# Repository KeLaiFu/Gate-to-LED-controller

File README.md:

# Gate-to-LED-controller
Edit of Jonathan Bedrava's LED controller (https://github.com/JonathanBedrava/eurorack-cv-led-strip-controller)

Current Status: Untested, although previous versions of an almost identical layout worked fine.

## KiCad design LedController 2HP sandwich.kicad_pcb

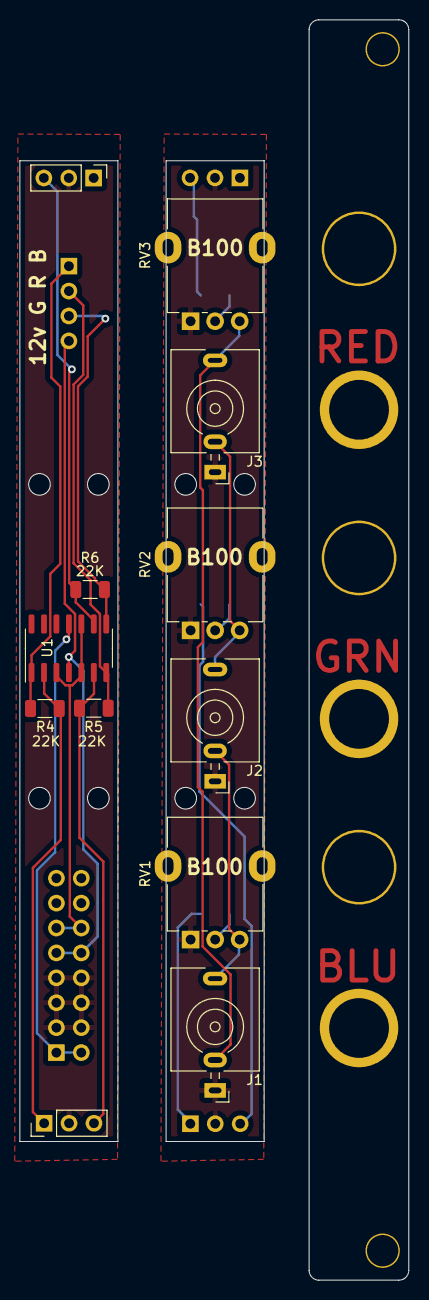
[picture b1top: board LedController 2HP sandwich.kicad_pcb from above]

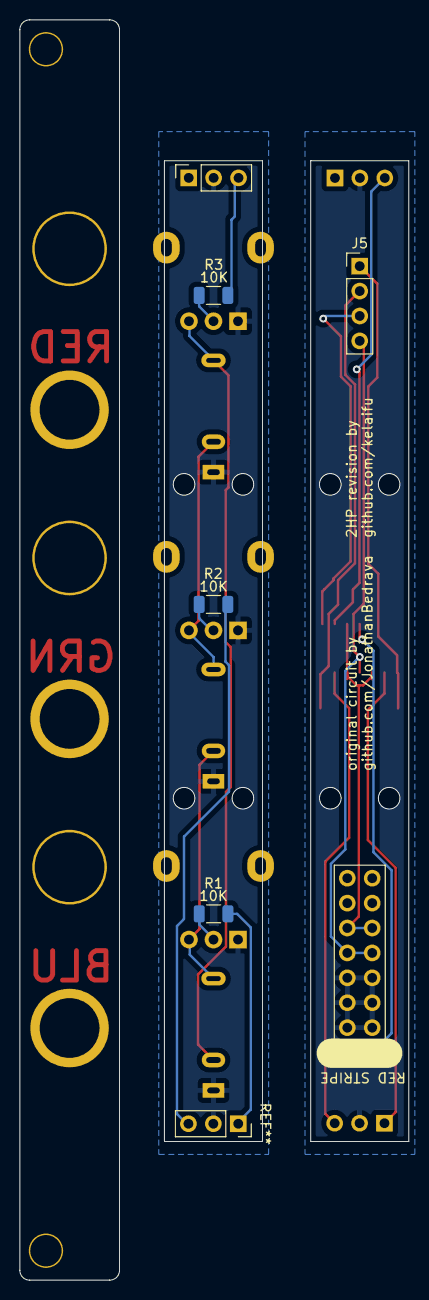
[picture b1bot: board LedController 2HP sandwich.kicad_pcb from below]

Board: 2 copper layers, 39.7 x 128.5 mm, 16 parts (5 on the bottom side), 16 nets.

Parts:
J1, J2, J3: AudioJack2; 3.5mm_tip_switch_thonkiconn
J4: Conn_02x08_Odd_Even; PinHeader_2x08_P2.54mm_Vertical
J5: Conn_01x04_Female; PinHeader_1x04_P2.54mm_Vertical
R1, R2, R3: 10K; R_1206_3216Metric
R4, R5, R6: 22K; R_1206_3216Metric
RV1, RV2, RV3: 100K; Potentiometer_Alpha_RD901F-40-00D_Single_Vertical
U1: TL084; SOIC-14_3.9x8.7mm_P1.27mm
U$1: EURORACK_PANEL2HP; EURORACK2HPPANEL

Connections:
+5V: J4.11, J4.12, U1.3 (+), U1.5 (+), U1.10 (+)
+12V: J4.9, J4.10, J5.4, U1.4 (V+)
-12V: J4.1, J4.2, U1.11 (V-)
GND: J1.S, J2.S, J3.S, J4.3, J4.4, J4.5, J4.6, J4.7, J4.8, RV1.1, RV2.1, RV3.1
unnamed: J1.T, J2.TN, RV1.3
unnamed: J2.T, J3.TN, RV2.3
unnamed: J1.TN, J3.T, RV3.3
unnamed: J5.1, R4.2, U1.1
unnamed: J5.2, R5.2, U1.7
unnamed: J5.3, R6.2, U1.8
unnamed: R1.1, R4.1, U1.2 (-)
unnamed: R1.2, RV1.2
unnamed: R2.1, R5.1, U1.6 (-)
unnamed: R2.2, RV2.2
unnamed: R3.1, R6.1, U1.9 (-)
unnamed: R3.2, RV3.2

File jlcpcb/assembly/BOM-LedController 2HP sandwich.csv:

Comment,Designator,Footprint,LCSC
22K,R4,R_1206_3216Metric,
22K,R5,R_1206_3216Metric,
22K,R6,R_1206_3216Metric,
100K,RV2,Potentiometer_Alpha_RD901F-40-00D_Single_Vertical,
100K,RV3,Potentiometer_Alpha_RD901F-40-00D_Single_Vertical,
TL084,U1,SOIC-14_3.9x8.7mm_P1.27mm,
AudioJack2,J1,3.5mm_tip_switch_thonkiconn,
AudioJack2,J2,3.5mm_tip_switch_thonkiconn,
AudioJack2,J3,3.5mm_tip_switch_thonkiconn,
100K,RV1,Potentiometer_Alpha_RD901F-40-00D_Single_Vertical,
10K,R1,R_1206_3216Metric,
10K,R2,R_1206_3216Metric,
10K,R3,R_1206_3216Metric,
Conn_02x08_Odd_Even,J4,PinHeader_2x08_P2.54mm_Vertical,
Conn_01x04_Female,J5,PinHeader_1x04_P2.54mm_Vertical,
